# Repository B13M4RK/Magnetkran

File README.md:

<div align="center">

  # Magnetkran
  ### Schulinternes Entwicklungsprojekt • Hardware & Steuerung

  **Autor:** Paul Dreißig

</div>

---

## 🏗️ Dokumentation & Projektstruktur

Das ist das zentrale Repository für das **Magnetkran-Projekt**. Hier findest du alle Konstruktionspläne, Schaltpläne, Quellcodes und Präsentationen:

<details>
<summary><b>📄 Dokumente & Präsentationen</b></summary>
<br>

* [📄 Projektbeschreibung](./docs/projekt-beschreibung.odt)
* [📓 Logbuch (PDF)](./docs/logbuch.pdf)
* [📊 Materialliste & Kosten](./docs/materialliste-und-kosten.ods)
* [📝 Handout zur Präsentation](./docs/presentation/handout.odt)

Präsentation (Pitch)
* [📽️ Pitch-Präsentation (PDF)](./docs/presentation/pitch-präsentation.pdf)
* [📽️ Pitch-Präsentation (PPTX)](./docs/presentation/pitch-präsentation.pptx)

</details>

<details>
<summary><b>⚡ Elektronik & Schaltpläne</b></summary>
<br>

* [📄 Schaltplan (Farbe)](./electronics/schaltplan.pdf)
* [📄 Schaltplan (Schwarz/Weiß)](./electronics/schaltplan-b%26w.pdf)
* [🎛️ KiCad Projektordner](./electronics/kicad-magnetkran/)

</details>

<details>
<summary><b>💻 Firmware & Steuerung</b></summary>

* [💻 Firmware Quellcode](./firmware/kran-oben-magnetkran/)

</details>

<details>
<summary><b>📐 Mechanik & Physik</b></summary>

* [📐 Kräfteverteilung am Ausleger (PDF)](./mechanics/force-distribution-on-crane.pdf)

</details>

<details>
<summary><b>🖼️ Fotodokumentation & Prototypen</b></summary>

* [📷 Bauphasen & Bildeindrücke](./img/)
* [✂️ Papiermodell](./img/papiermodell-magnetkran/)

</details>

---

## 🛠️ Features & Technische Details

* **Motor- & Magnetansteuerung:** Eigenbau-H-Brücken zur präzisen Ansteuerung der Motoren sowie des Elektromagneten.
* **Signalverarbeitung:** IR-Empfänger zur drahtlosen Steuerung des Krans.
* **Custom PCB:** Hardware-Entwurf und Layout erstellt mit KiCad.
* **Mechanische Analyse:** Vektoriell berechnete Kräfteverteilung am Kranausleger.

---

## 📥 Projekt Herunterladen

Git Clone (Repository klonen)

```bash
cd Downloads
git clone [https://github.com/B13M4RK/Magnetkran.git](https://github.com/B13M4RK/Magnetkran.git)

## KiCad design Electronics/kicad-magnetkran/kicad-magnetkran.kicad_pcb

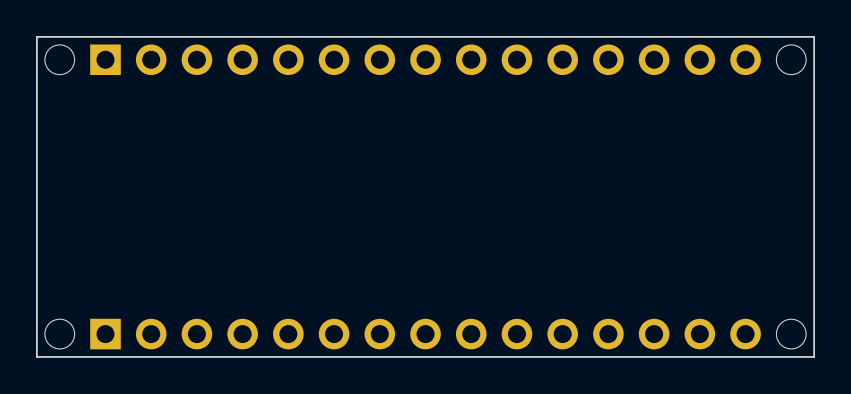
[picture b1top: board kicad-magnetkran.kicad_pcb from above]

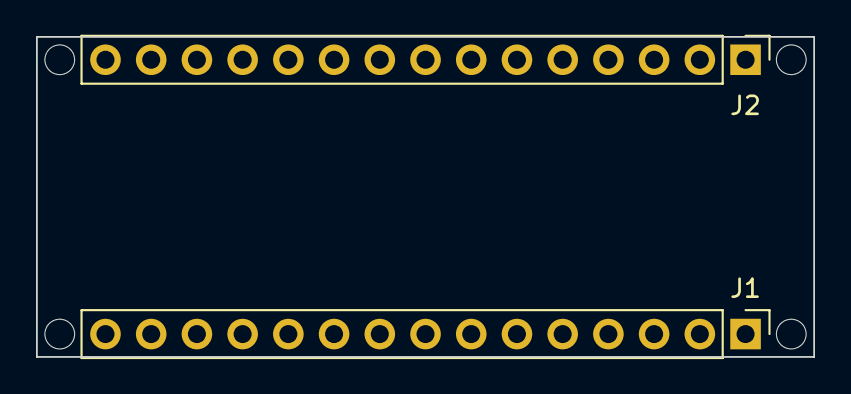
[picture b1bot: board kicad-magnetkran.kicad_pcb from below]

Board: 2 copper layers, 43.2 x 17.8 mm, 6 parts (2 on the bottom side), 2 nets, no tracks yet.

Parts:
J1: Analog; PinHeader_1x15_P2.54mm_Vertical
J2: Digital; PinHeader_1x15_P2.54mm_Vertical
MH1, MH2, MH3, MH4: MountingHole_65mil

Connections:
/~RESET: J1.13, J2.13
GND: J1.14, J2.12

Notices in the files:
README.md:
License: MIT
